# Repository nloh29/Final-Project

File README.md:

# Final-Project

## Overview:
  Currently, the most common mode of travel around campus is by walking long distances in a short amount of time. This can be a very time consuming and energy consuming process that would greatly benefit from a more efficient mode of transportation. The goal of this project is to create an electric skateboard that allows students to move around campus in a more timely manner that is cheaper, lasts longer, goes faster, and is safer than the current equivalent. This will require firmware to control the board wirelessly using two microcontrollers, the use of motors and motor driver circuits to physically drive the board, charging via USB-C for easier charging access without the need for a specifically dedicated charging solution, and power distribution/regulation for all of the components involved using a safer battery type.

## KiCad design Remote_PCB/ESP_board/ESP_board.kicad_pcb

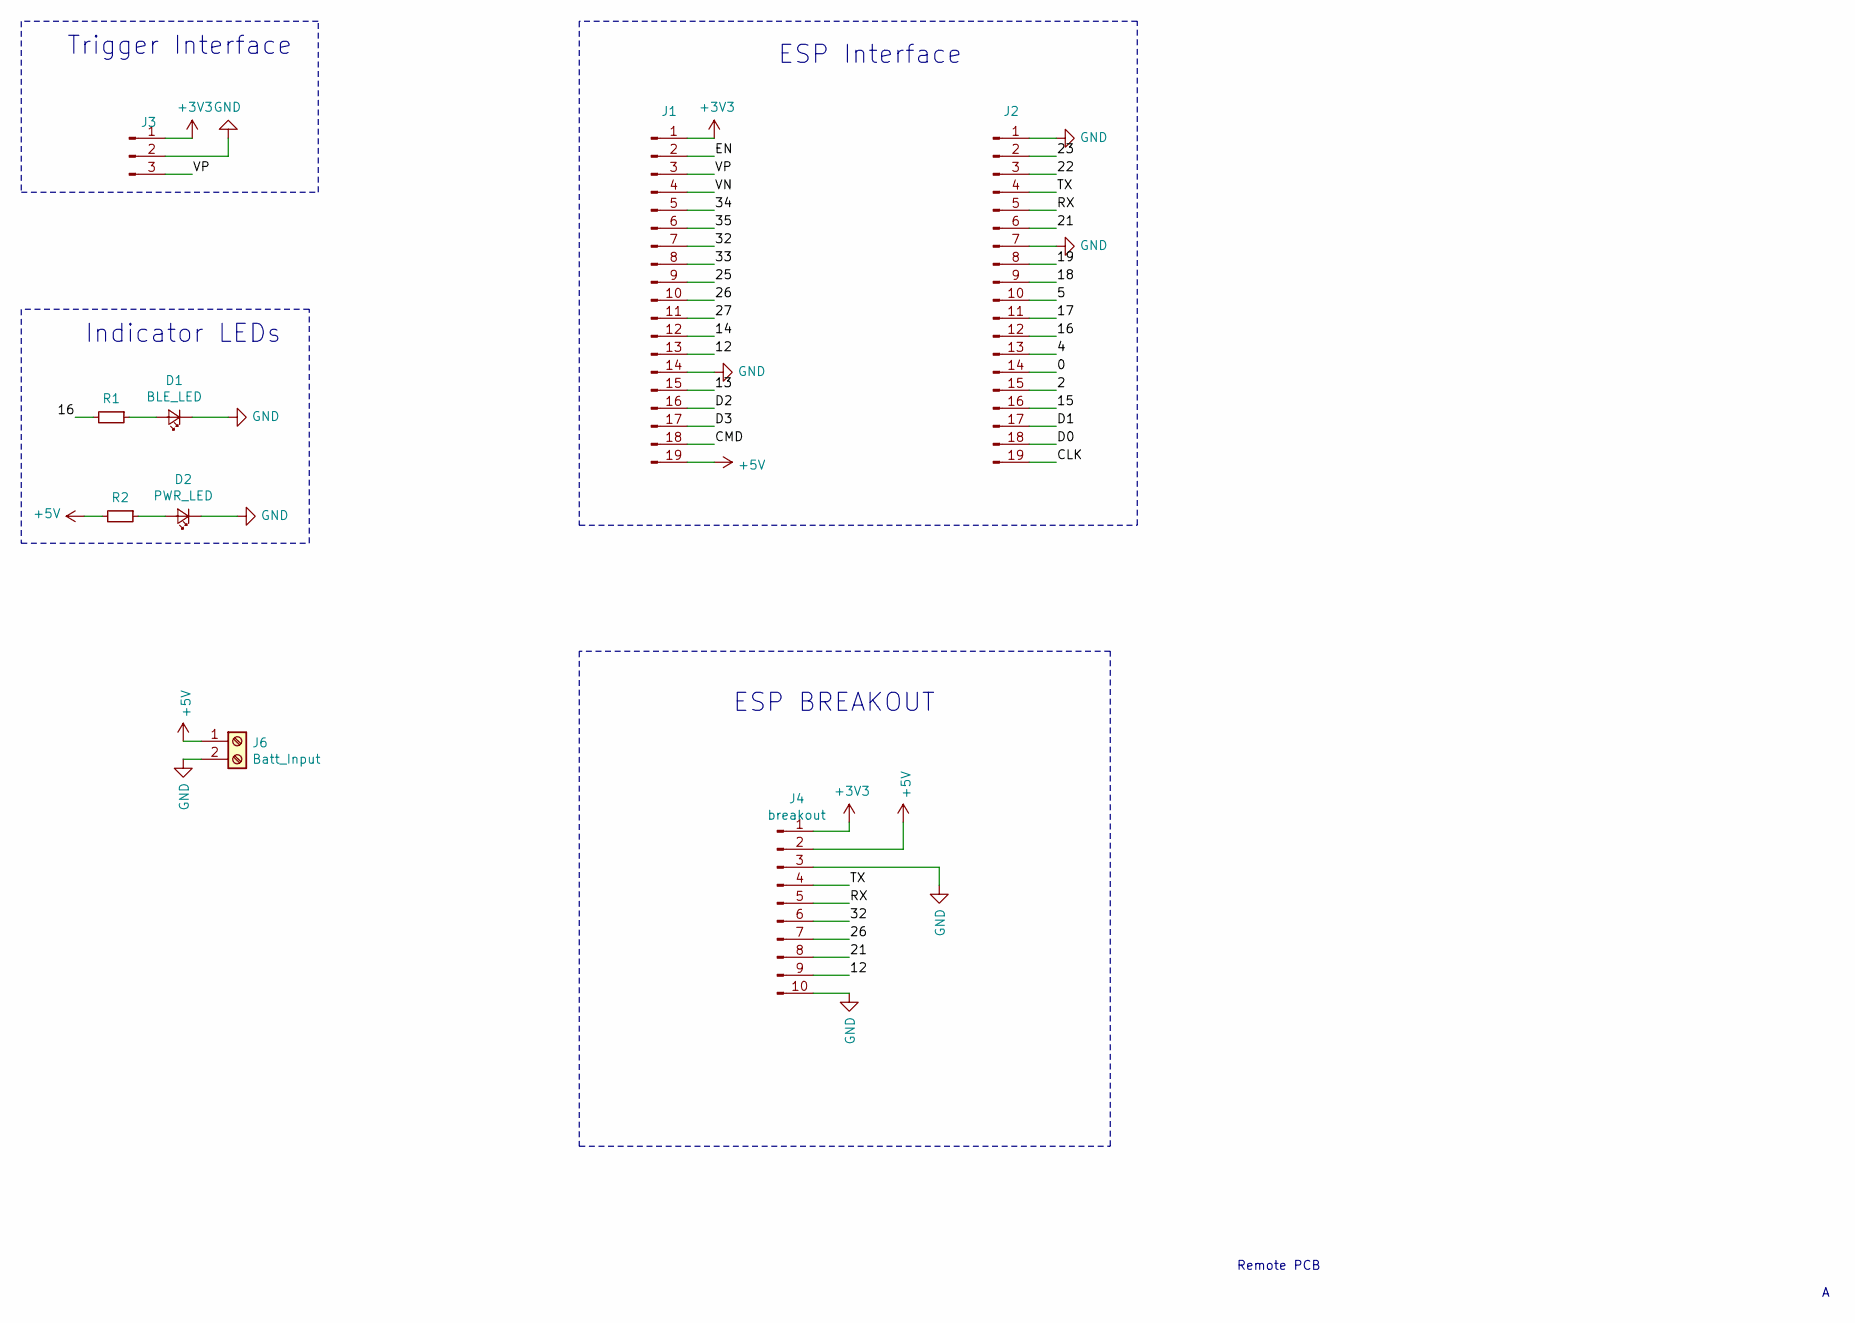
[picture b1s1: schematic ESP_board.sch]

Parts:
D1: BLE_LED; LED_D2.0mm_W4.0mm_H2.8mm_FlatTop
D2: PWR_LED; LED_D2.0mm_W4.0mm_H2.8mm_FlatTop
J1: leftside; Pin_Header_Straight_1x19_Pitch2.54mm
J2: rightside; Pin_Header_Straight_1x19_Pitch2.54mm
J3: Conn_01x03_Male; Pin_Header_Straight_1x03_Pitch2.54mm
J4: breakout; Pin_Header_Straight_1x10_Pitch2.54mm
J6: Batt_Input; TerminalBlock_bornier-2_P5.08mm
R1, R2: R_Small; R_0603_HandSoldering

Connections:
+3V3: J1.1, J3.1, J4.1
+5V: J1.19, J4.2, J6.1, R2.2
/0: J2.14
/2: J2.15
/4: J2.13
/5: J2.10
/12: J1.13, J4.9
/13: J1.15
/14: J1.12
/15: J2.16
/16: J2.12, R1.2
/17: J2.11
/18: J2.9
/19: J2.8
/21: J2.6, J4.8
/22: J2.3
/23: J2.2
/25: J1.9
/26: J1.10, J4.7
/27: J1.11
/32: J1.7, J4.6
/33: J1.8
/34: J1.5
/35: J1.6
/CLK: J2.19
/CMD: J1.18
/D0: J2.18
/D1: J2.17
/D2: J1.16
/D3: J1.17
/EN: J1.2
/RX: J2.5, J4.5
/TX: J2.4, J4.4
/VN: J1.4
/VP: J1.3, J3.3
GND: D1.1 (K), D2.1 (K), J1.14, J2.1, J2.7, J3.2, J4.3, J4.10, J6.2
unnamed: D1.2 (A), R1.1
unnamed: D2.2 (A), R2.1

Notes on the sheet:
Remote PCB
ESP Interface
Trigger Interface
Indicator LEDs
ESP BREAKOUT

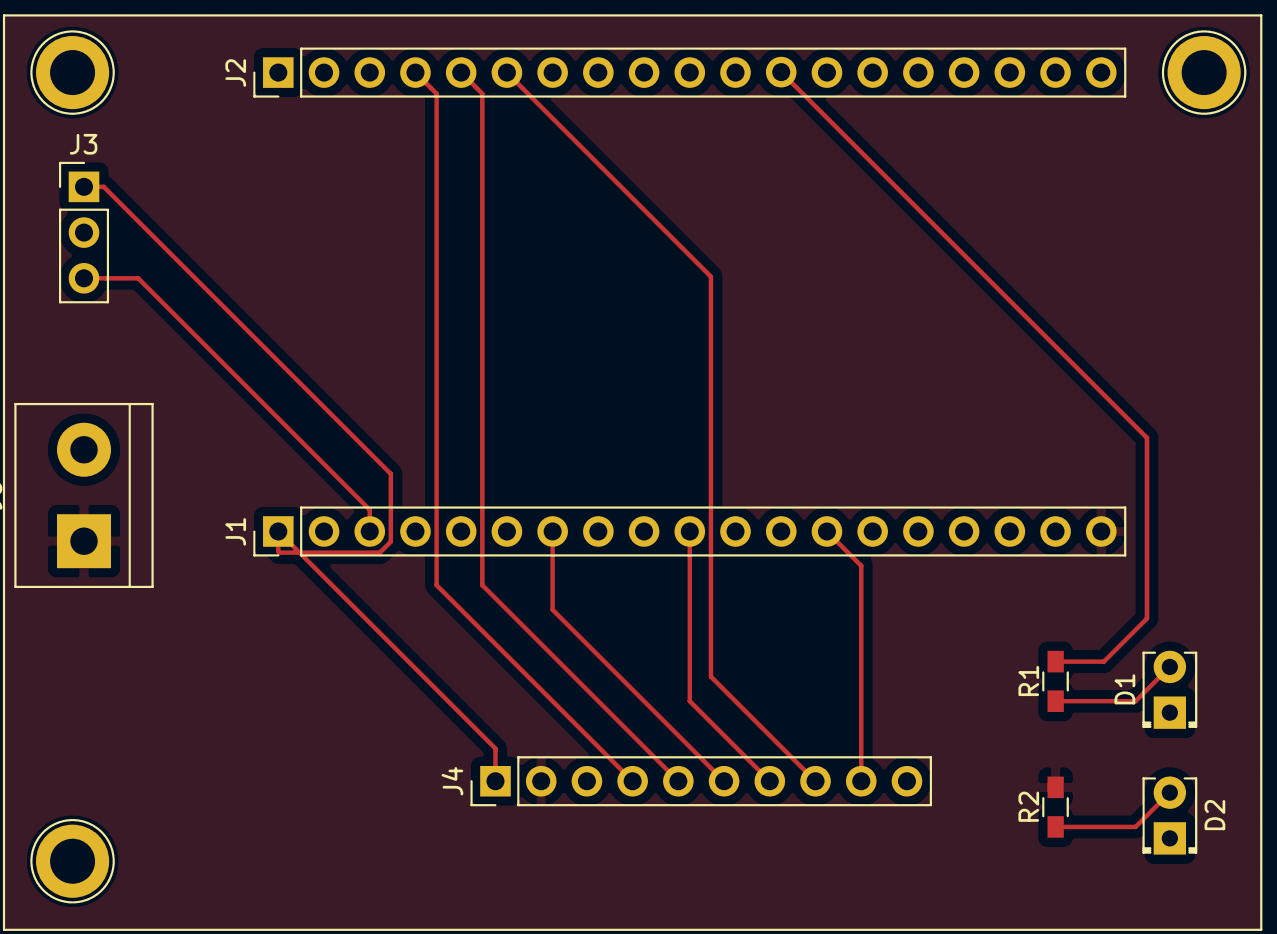
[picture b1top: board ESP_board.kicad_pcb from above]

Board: 2 copper layers, 9 parts (0 on the bottom side), 13 nets.

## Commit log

2019-06-28 beginning portion of schematic
2019-08-06 Create Remote_Firmware
2019-08-06 Added Folders
2019-08-06 Added Firmware
2019-08-06 added proper path
2019-08-06 Added .cydsn project path
2019-08-06 Added a notes file to stuff you are stuck on or found
2019-08-06 Deleted personal project file
2019-08-29 added BT transmit to triggertest
2019-09-10 updated schematic
2019-10-06 Add files via upload
    Remote Firmware that reads adc values and transmits
2019-10-06 Added Remote Model
2019-10-06 Added Remote Top and Bottom Piece
2019-10-06 Added ESP32_Server via upload
    adds averaging for the input ADC values
2019-10-06 Added ESP32_Client added via upload
2019-10-16 Added ESP32_Clientv2.0
    fixed long disconnect timeout using notify and a looping timeout variable. Disconnects after ~100ms of no notifications
2019-10-23 updated remote
    made remote bigger and added battery housing model to fit in the remote.
2019-10-24 Added remote assembly and STL
    Added remote assembly with battery holder, USB-C cut out, ESP32 Board mounts.
    Also added the STL file so that we can print it.
2019-10-26 Added new schematic
    Breakout board for the remote. Board is in intermediate stage of the layout process.
2019-10-28 Finished Layout
2019-10-28 BOM
    Added Final BOM for the remote board.
2019-11-20 Added remote model
    Added improved model design that is larger and has a bigger opening for the trigger. Also extended the remote handle so that the battery circuit will fit.
